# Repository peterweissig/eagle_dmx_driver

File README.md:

# eagle_dmx_driver
Simple galvanic decoupled dmx-driver

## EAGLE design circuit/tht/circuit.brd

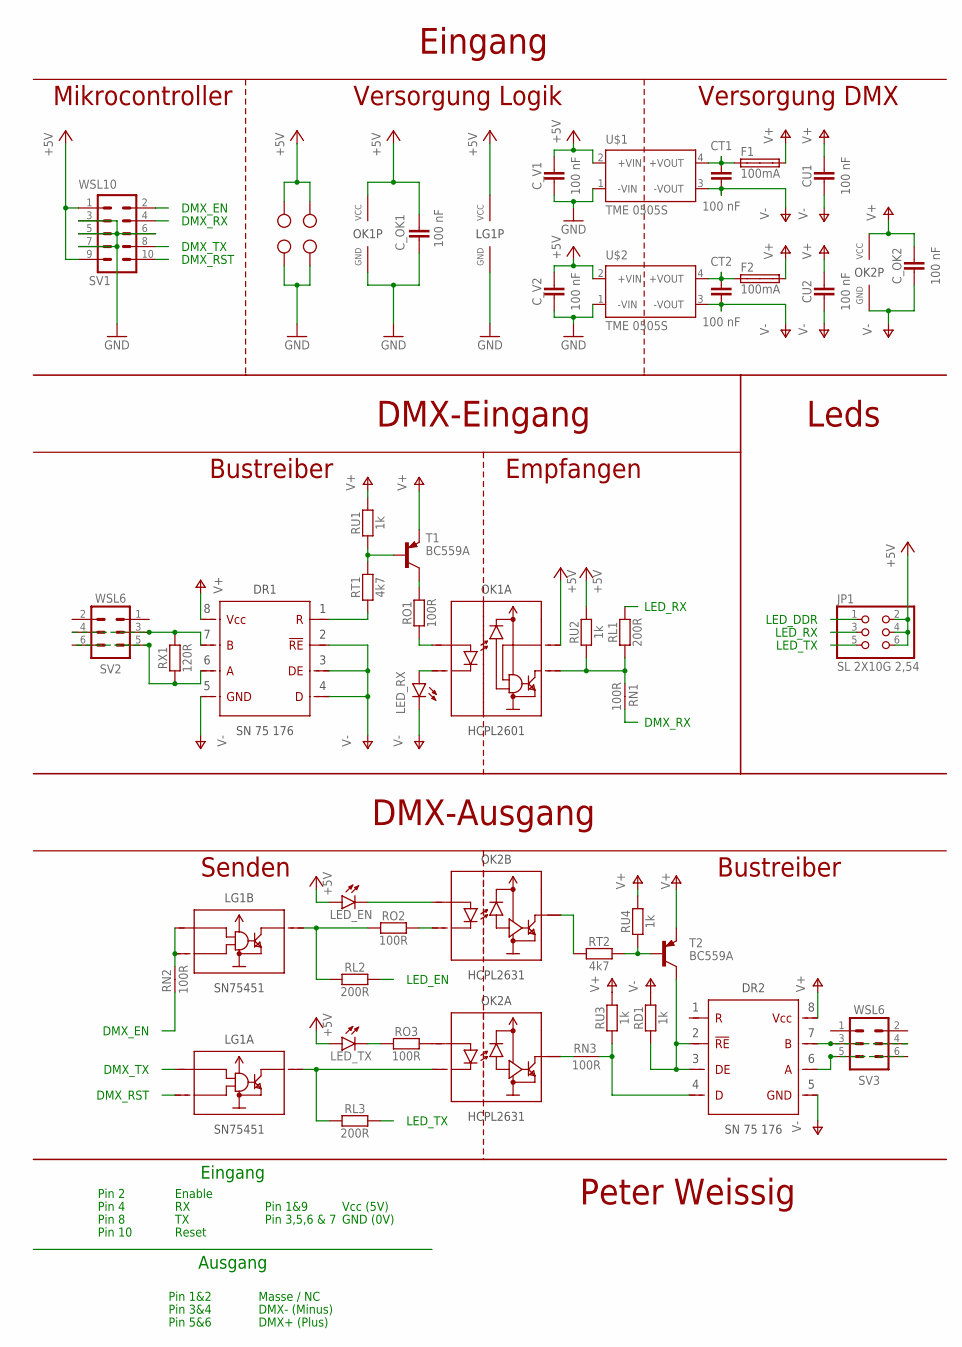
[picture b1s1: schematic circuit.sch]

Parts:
CT1, CT2: 100 nF; C_THT_2
CU1, CU2: 100 nF; C_THT_2
C_OK1, C_OK2: 100 nF; C_THT_2
C_V1, C_V2: 100 nF; C_THT_2
DR1, DR2: SN75 176; IC_DIL08
F1, F2: 100mA; SHK20L
JP1: SL 2X10G 2,54; 2X03
LED_EN: LED-3MM; LED_3MM
LED_RX: LED-3MM; LED_3MM
LED_TX: LED-3MM; LED_3MM
LG1: SN75451; IC_DIL08_OUT
OK1: HCPL2601; IC_DIL08_OUT
OK2: HCPL2631; IC_DIL08_OUT
RD1: 1k; R_THT_4
RL1, RL2, RL3: 200R; R_THT_4
RN1, RN2, RN3: 100R; R_THT_4
RO1, RO2, RO3: 100R; R_THT_4
RT1, RT2: 4k7; R_THT_4
RU1, RU2, RU3, RU4: 1k; R_THT_4
RX1: 120R; R_THT_4
SV1: WSL10; STECKER_WANNE_10
SV2, SV3: WSL6; STECKER_WANNE_6
T1, T2: BC559A; TO92-EBC
U$1, U$2: TME 0505S; TRACO_TME_1
X1, X2: AKL101-2; W237-102

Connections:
+5V: C_OK1.1, C_V1.1, C_V2.1, JP1.2, JP1.4, JP1.6, LED_EN.A, LED_TX.A, LG1.8 (VCC), OK1.7 (I_EN), OK1.8 (VCC), RU2.2, SV1.1, SV1.9, U$1.2 (+VIN), U$2.2 (+VIN), X1.1, X2.2
DMX_DDR_1_O1: DR2.2, DR2.3, RD1.2, T2.C
DMX_EN: RN2.2, SV1.2
DMX_N_1: DR1.7, RX1.1, SV2.3, SV2.4
DMX_N_2: DR2.7, SV3.3, SV3.4
DMX_P_1: DR1.6, RX1.2, SV2.5, SV2.6
DMX_P_2: DR2.6, SV3.5, SV3.6
DMX_READ_1_O: DR1.1, RT1.2
DMX_RST: LG1.2 (I_2), SV1.10
DMX_RX: RN1.1, SV1.4
DMX_TX: LG1.1 (I_1), SV1.8
GND: C_OK1.2, C_V1.2, C_V2.2, LG1.4 (GND), OK1.5 (GND), SV1.3, SV1.5, SV1.6, SV1.7, U$1.1 (-VIN), U$2.1 (-VIN), X1.2, X2.1
GND_RX: CT1.2, CU1.2, DR1.2, DR1.3, DR1.4, DR1.5, LED_RX.K (C), U$1.3 (-VOUT)
GND_TX: CT2.2, CU2.2, C_OK2.1, DR2.5, OK2.5 (GND), RD1.1, U$2.3 (-VOUT)
LED_EN: JP1.1, RL2.2
LED_RX: JP1.3, RL1.1
LED_TX: JP1.5, RL3.2
unnamed: OK1.6 (O), RL1.2, RN1.2, RU2.1
unnamed: OK2.6 (O), RT2.2
unnamed: OK2.7 (O), RN3.2
unnamed: DR2.4, RN3.1, RU3.2
unnamed: RT1.1, RU1.2, T1.B
unnamed: RT2.1, RU4.2, T2.B
unnamed: LG1.3 (O), OK2.2 (I_K), RL3.1
unnamed: OK2.1 (I_A), RO3.2
unnamed: OK2.3 (I_K), RO2.2
unnamed: LED_TX.K (C), RO3.1
unnamed: CT1.1, F1.1A, U$1.4 (+VOUT)
unnamed: LG1.5 (O), RL2.1, RO2.1
unnamed: LED_EN.K (C), OK2.4 (I_A)
unnamed: LED_RX.A, OK1.3 (I_K)
unnamed: OK1.2 (I_A), RO1.1
unnamed: RO1.2, T1.C
unnamed: CT2.1, F2.1A, U$2.4 (+VOUT)
N$_14: LG1.6 (I_1), LG1.7 (I_2), RN2.1
VCC_RX: CU1.1, DR1.8, F1.2A, RU1.1, T1.E
VCC_TX: CU2.1, C_OK2.2, DR2.8, F2.2A, OK2.8 (VCC), RU3.1, RU4.1, T2.E

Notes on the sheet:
DMX-Eingang
DMX_RX
Eingang
DMX_TX
DMX_EN
Peter Weissig
Empfangen
Bustreiber
LED_RX
DMX-Ausgang
Mikrocontroller
Versorgung DMX
LED_TX
LED_DDR
Senden
LED_EN
Ausgang
Pin 1&2
Pin 3&4
Pin 5&6
Masse / NC
DMX- (Minus)
DMX+ (Plus)
Pin 1&9
Pin 3,5,6 & 7
Vcc (5V)
GND (0V)
Pin 4
Pin 8
Pin 10
Reset
DMX_RST
Versorgung Logik
Leds
Pin 2
Enable

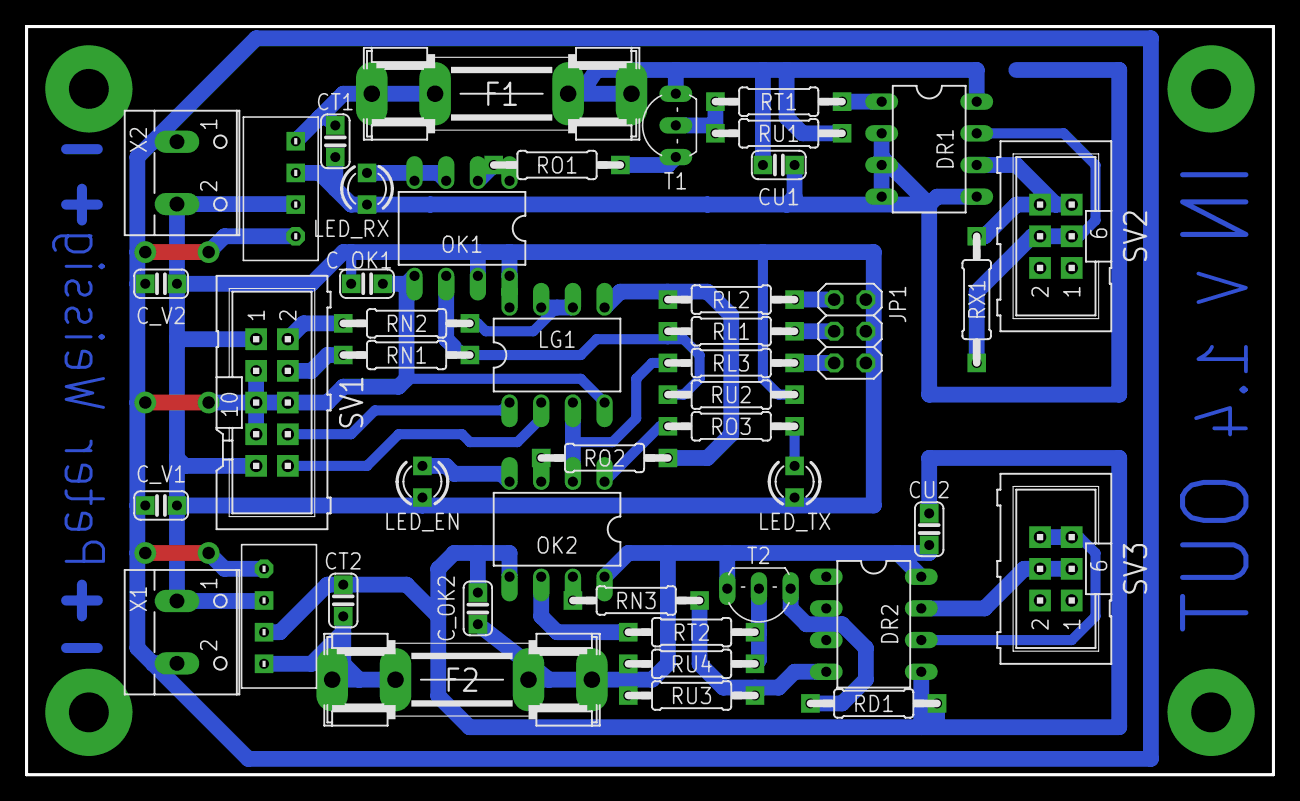
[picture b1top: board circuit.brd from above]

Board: 2 copper layers, 100.0 x 60.0 mm, 45 parts (0 on the bottom side), 37 nets.
